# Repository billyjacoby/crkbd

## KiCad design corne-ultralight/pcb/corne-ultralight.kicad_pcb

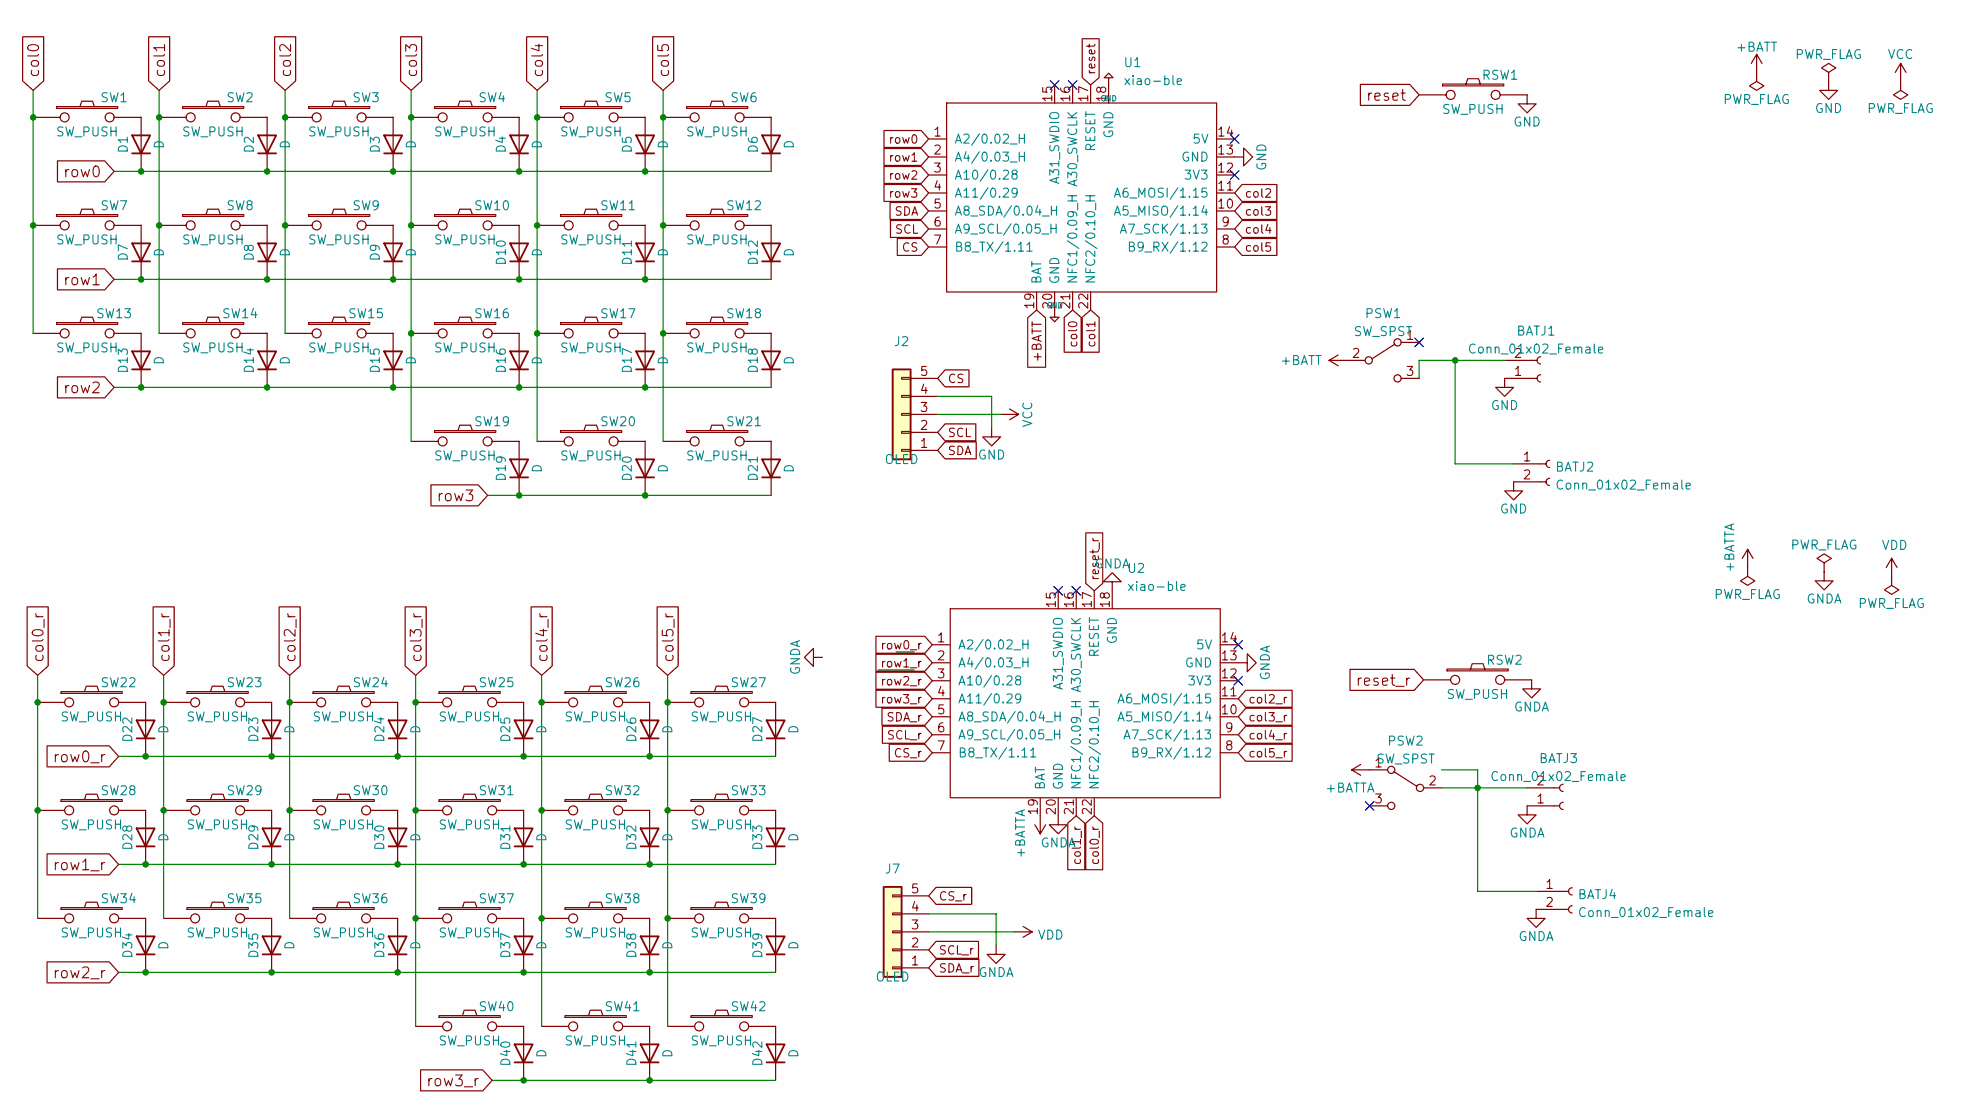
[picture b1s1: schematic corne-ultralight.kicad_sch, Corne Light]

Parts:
BATJ1, BATJ3: Conn_01x02_Female; PinHeader_1x02_P2.54mm_Vertical
BATJ2, BATJ4: Conn_01x02_Female; JST_PH_S2B-PH-K_1x02_P2.00mm_Horizontal
D1, D2, D3, D4, D5, D6, D7, D8, D9, D10, D11, D12, D13, D14, D15, D16, D17, D18, D19, D20, D21, D22, D23, D24, D25, D26, D27, D28, D29, D30, D31, D32, D33, D34, D35, D36, D37, D38, D39, D40, D41, D42: D; D3_TH_SMD_v2
J2, J7: OLED; nice_view_1side
PSW1, PSW2: SW_SPST; SW_SPDT_PCM12
RSW1, RSW2: SW_PUSH; ResetSW_1side
SW1, SW2, SW3, SW4, SW5, SW6, SW7, SW8, SW9, SW10, SW11, SW12, SW13, SW14, SW15, SW16, SW17, SW18, SW19, SW20, SW22, SW23, SW24, SW25, SW26, SW27, SW28, SW29, SW30, SW31, SW32, SW33, SW34, SW35, SW36, SW37, SW38, SW39, SW40, SW41: SW_PUSH; CherryMX_Choc_Hotswap_BACKONLY
SW21, SW42: SW_PUSH; CherryMX_Choc_Hotswap_1.5u_BACKONLY
U1, U2: xiao-ble; xiao-ble-tht

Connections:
+BATT: PSW1.2 (B), U1.19 (BAT)
+BATTA: PSW2.1 (A), U2.19 (BAT)
CS: J2.5, U1.7 (B8_TX/1.11)
CS_r: J7.5, U2.7 (B8_TX/1.11)
GNDA: BATJ3.1, BATJ4.2, J7.4, RSW2.2, U2.13 (GND), U2.18 (GND), U2.20 (GND); also elsewhere on the board
unnamed: BATJ1.2, BATJ2.1, PSW1.3 (C)
unnamed: BATJ3.2, BATJ4.1, PSW2.2 (B)
unnamed: D1.2 (A), SW1.2
unnamed: D2.2 (A), SW2.2
unnamed: D3.2 (A), SW3.2
unnamed: D4.2 (A), SW4.2
unnamed: D5.2 (A), SW5.2
unnamed: D6.2 (A), SW6.2
unnamed: D7.2 (A), SW7.2
unnamed: D8.2 (A), SW8.2
unnamed: D9.2 (A), SW9.2
unnamed: D10.2 (A), SW10.2
unnamed: D11.2 (A), SW11.2
unnamed: D12.2 (A), SW12.2
unnamed: D13.2 (A), SW13.2
unnamed: D14.2 (A), SW14.2
unnamed: D15.2 (A), SW15.2
unnamed: D16.2 (A), SW16.2
unnamed: D17.2 (A), SW17.2
unnamed: D18.2 (A), SW18.2
unnamed: D19.2 (A), SW19.2
unnamed: D20.2 (A), SW20.2
unnamed: D21.2 (A), SW21.2
unnamed: D22.2 (A), SW22.2
unnamed: D23.2 (A), SW23.2
unnamed: D24.2 (A), SW24.2
unnamed: D25.2 (A), SW25.2
unnamed: D26.2 (A), SW26.2
unnamed: D27.2 (A), SW27.2
unnamed: D28.2 (A), SW28.2
unnamed: D29.2 (A), SW29.2
unnamed: D30.2 (A), SW30.2
unnamed: D31.2 (A), SW31.2
unnamed: D32.2 (A), SW32.2
unnamed: D33.2 (A), SW33.2
unnamed: D34.2 (A), SW34.2
unnamed: D35.2 (A), SW35.2
unnamed: D36.2 (A), SW36.2
unnamed: D37.2 (A), SW37.2
unnamed: D38.2 (A), SW38.2
unnamed: D39.2 (A), SW39.2
unnamed: D40.2 (A), SW40.2
unnamed: D41.2 (A), SW41.2
unnamed: D42.2 (A), SW42.2
SCL: J2.2, U1.6 (A9_SCL/0.05_H)
SCL_r: J7.2, U2.6 (A9_SCL/0.05_H)
SDA: J2.1, U1.5 (A8_SDA/0.04_H)
SDA_r: J7.1, U2.5 (A8_SDA/0.04_H)
VCC: J2.3; also elsewhere on the board
VDD: J7.3; also elsewhere on the board
col0: SW1.1, SW7.1, SW13.1, U1.21 (NFC1/0.09_H)
col0_r: SW22.1, SW28.1, SW34.1, U2.22 (NFC2/0.10_H)
col1: SW2.1, SW8.1, SW14.1, U1.22 (NFC2/0.10_H)
col1_r: SW23.1, SW29.1, SW35.1, U2.21 (NFC1/0.09_H)
col2: SW3.1, SW9.1, SW15.1, U1.11 (A6_MOSI/1.15)
col2_r: SW24.1, SW30.1, SW36.1, U2.11 (A6_MOSI/1.15)
col3: SW4.1, SW10.1, SW16.1, SW19.1, U1.10 (A5_MISO/1.14)
col3_r: SW25.1, SW31.1, SW37.1, SW40.1, U2.10 (A5_MISO/1.14)
col4: SW5.1, SW11.1, SW17.1, SW20.1, U1.9 (A7_SCK/1.13)
col4_r: SW26.1, SW32.1, SW38.1, SW41.1, U2.9 (A7_SCK/1.13)
col5: SW6.1, SW12.1, SW18.1, SW21.1, U1.8 (B9_RX/1.12)
col5_r: SW27.1, SW33.1, SW39.1, SW42.1, U2.8 (B9_RX/1.12)
reset: RSW1.1, U1.17 (RESET)
reset_r: RSW2.1, U2.17 (RESET)
row0: D1.1 (K), D2.1 (K), D3.1 (K), D4.1 (K), D5.1 (K), D6.1 (K), U1.1 (A2/0.02_H)
row0_r: D22.1 (K), D23.1 (K), D24.1 (K), D25.1 (K), D26.1 (K), D27.1 (K), U2.1 (A2/0.02_H)
row1: D7.1 (K), D8.1 (K), D9.1 (K), D10.1 (K), D11.1 (K), D12.1 (K), U1.2 (A4/0.03_H)
row1_r: D28.1 (K), D29.1 (K), D30.1 (K), D31.1 (K), D32.1 (K), D33.1 (K), U2.2 (A4/0.03_H)
row2: D13.1 (K), D14.1 (K), D15.1 (K), D16.1 (K), D17.1 (K), D18.1 (K), U1.3 (A10/0.28)
row2_r: D34.1 (K), D35.1 (K), D36.1 (K), D37.1 (K), D38.1 (K), D39.1 (K), U2.3 (A10/0.28)
row3: D19.1 (K), D20.1 (K), D21.1 (K), U1.4 (A11/0.29)
row3_r: D40.1 (K), D41.1 (K), D42.1 (K), U2.4 (A11/0.29)

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
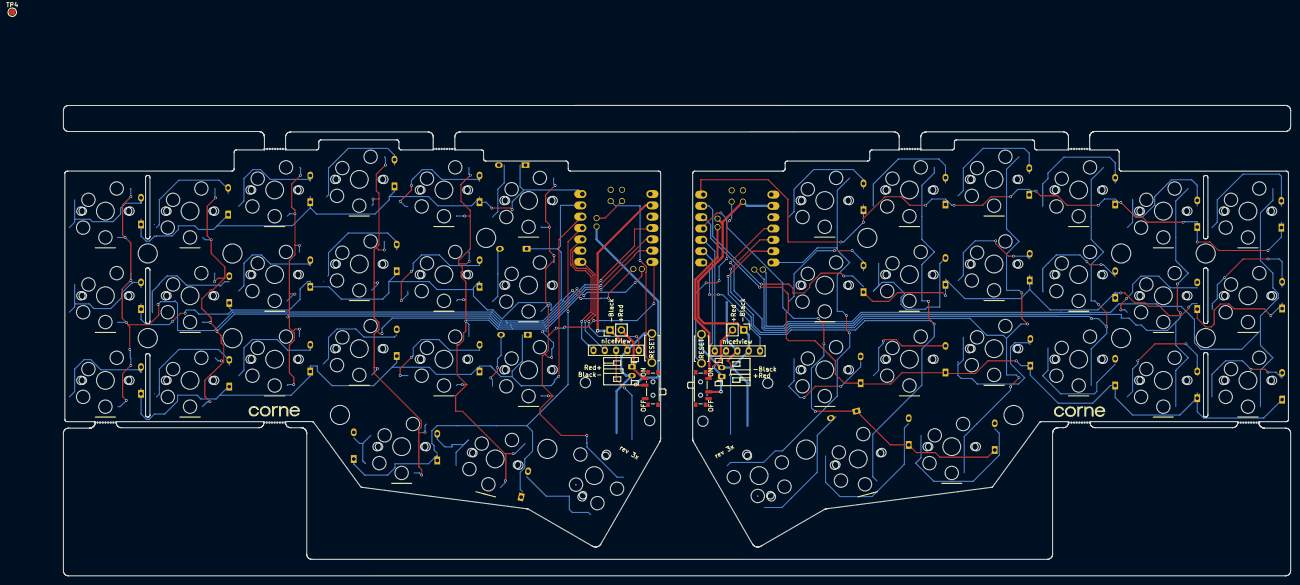
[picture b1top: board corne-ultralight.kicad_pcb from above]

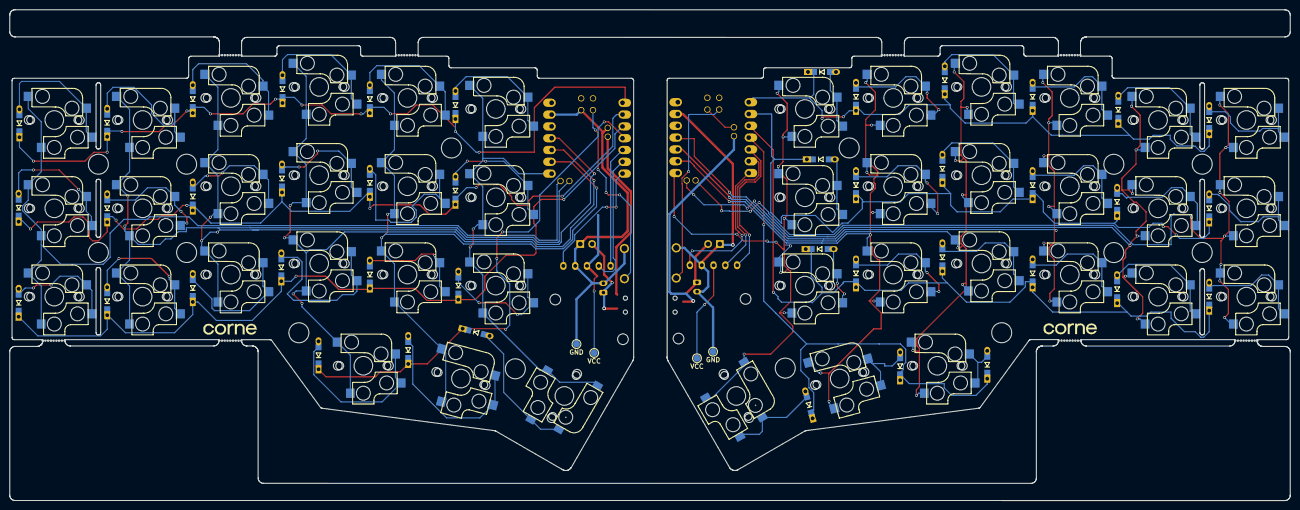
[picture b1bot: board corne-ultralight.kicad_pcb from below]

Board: 2 copper layers, 275.5 x 105.6 mm, 127 parts (62 on the bottom side), 79 nets.

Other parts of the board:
J5, J5#2, J5#3, J5#4, J5#5, J5#6, J5#7, J5#8: Breakaway_Tabs
Ref**: Val**; thread_m2
Ref**#2, Ref**#8, Ref**#9: Val**; thread_m2
Ref**#3, Ref**#4, Ref**#5, Ref**#6, Ref**#7, Ref**#10, Ref**#11, Ref**#12, Ref**#13, Ref**#14, Ref**#15, Ref**#16, Ref**#17, Ref**#18: Val**; spacer_m2
TP2, TP5: VCC; TestPoint_Pad_D1.5mm
TP3, TP6: GND; TestPoint_Pad_D1.5mm
TP4: RGB; TestPoint_Pad_D1.5mm

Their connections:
GNDA: TP6.1; also elsewhere on the board
VCC: TP2.1; also elsewhere on the board
VDD: TP5.1; also elsewhere on the board

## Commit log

2023-01-15 Right half changed to hotswaps
2023-01-15 TH Diodes
2023-01-15 Left side mostly routed
2023-02-06 Fixed flipped footprints
2023-02-06 removed text, update rev
2023-02-06 deleted left half of the board
2023-02-16 Added XIAO footprint
2023-02-16 Moved nice!view VCC to 3.3v
2023-02-16 rebased with proper right footprints
2023-02-25 Left side completed
2023-03-12 update footptint
